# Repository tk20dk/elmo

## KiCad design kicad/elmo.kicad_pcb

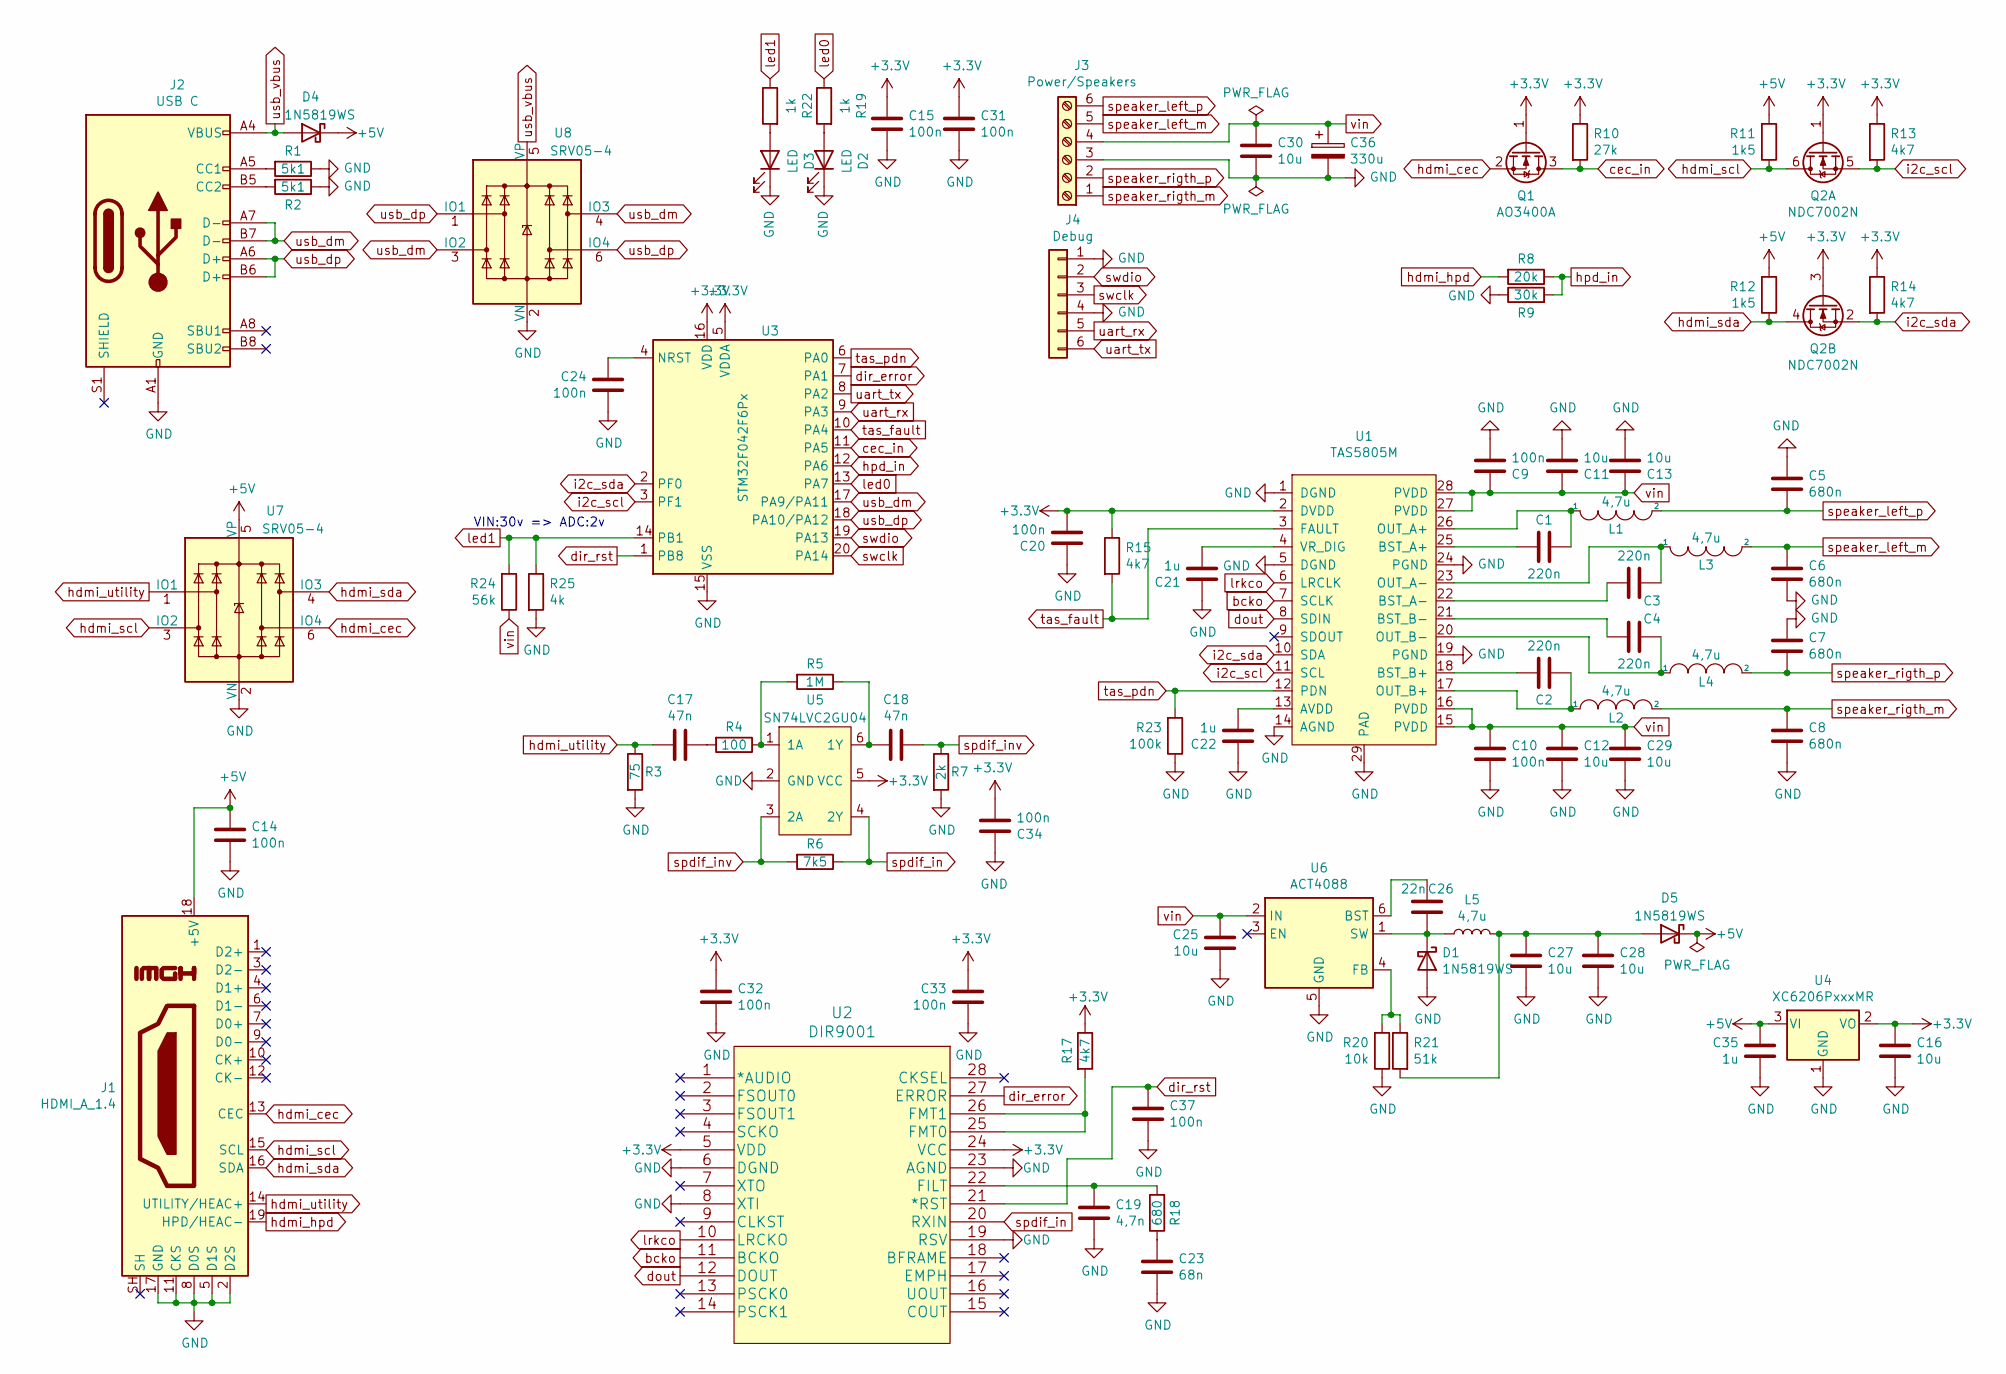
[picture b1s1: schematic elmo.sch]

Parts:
C1, C2, C3, C4: 220n; C_0603_1608Metric
C5, C6, C7, C8: 680n; C_0805_2012Metric
C9, C10, C14, C20: 100n; C_0603_1608Metric
C11, C12, C13, C16, C25, C27, C28, C29, C30: 10u; C_0805_2012Metric
C15, C24, C31, C32, C33, C34, C37: 100n; C_0402_1005Metric
C17, C18: 47n; C_0402_1005Metric
C19: 4,7n; C_0402_1005Metric
C21, C22, C35: 1u; C_0603_1608Metric
C23: 68n; C_0402_1005Metric
C26: 22n; C_0603_1608Metric
C36: 330u; CP_Elec_8x11.9
D1, D4, D5: 1N5819WS; D_SOD-323
D2, D3: LED; LED_0402_1005Metric
J1: HDMI_A_1.4; HDMI_A_19P
J2: USB C; USB_C_Receptacle_XKB_U262-16XN-4BVC11
J3: Power/Speakers; CONN_5MM_01x06
J4: Debug; PinHeader_1x06_P1.27mm_Vertical
L1, L2, L3, L4: 4,7u; L_6.3x6.3_H3
L5: 4,7u; L_4.1x4.1_H1.75
Q1: AO3400A; SOT-23
Q2: NDC7002N; SuperSOT-6
R1, R2: 5k1; R_0402_1005Metric
R3: 75; R_0402_1005Metric
R4: 100; R_0402_1005Metric
R5: 1M; R_0402_1005Metric
R6: 7k5; R_0402_1005Metric
R7: 2k; R_0402_1005Metric
R8: 20k; R_0402_1005Metric
R9: 30k; R_0402_1005Metric
R10: 27k; R_0402_1005Metric
R11, R12: 1k5; R_0402_1005Metric
R13, R14, R15, R17: 4k7; R_0402_1005Metric
R18: 680; R_0402_1005Metric
R19, R22: 1k; R_0402_1005Metric
R20: 10k; R_0402_1005Metric
R21: 51k; R_0402_1005Metric
R23: 100k; R_0402_1005Metric
R24: 56k; R_0402_1005Metric
R25: 4k; R_0402_1005Metric
U1: TAS5805M; HTSSOP-28-1EP_4.4x9.7mm_P0.65mm_EP3.4x9.5mm_Mask2.4x6.17mm_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
U2: DIR9001; TSSOP-28_4.4x9.7mm_P0.65mm
U3: STM32F042F6Px; TSSOP-20_4.4x6.5mm_P0.65mm
U4: XC6206PxxxMR; SOT-23
U5: SN74LVC2GU04; SOT-23-6
U6: ACT4088; SOT-23-6
U7, U8: SRV05-4; SOT-23-6

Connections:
+3V3: C15.1, C16.1, C20.2, C31.1, C32.1, C33.1, C34.2, Q1.1 (G), Q2.1 (G), Q2.3 (G), R10.1, R13.1, R14.1, R15.1, R17.1, U1.2 (DVDD), U2.5 (VDD), U2.24 (VCC), U3.5 (VDDA), U3.16 (VDD), U4.2 (VO), U5.5 (VCC)
+5V: C14.1, C35.1, D4.1 (K), D5.1 (K), J1.18 (+5V), R11.2, R12.2, U4.3 (VI), U7.5 (VP)
GND: C5.1, C6.2, C7.1, C8.2, C9.2, C10.2, C11.2, C12.2, C13.2, C14.2, C15.2, C16.2, C19.2, C20.1, C21.1, C22.1, C23.2, C24.2, C25.2, C27.2, C28.2, C29.2, C30.2, C31.2, C32.2, C33.2, C34.1, C35.2, C36.2, C37.2, D1.2 (A), D2.1 (K), D3.1 (K), J1.2 (D2S), J1.5 (D1S), J1.8 (D0S), J1.11 (CKS), J1.17 (GND), J2.A1 (GND), J2.A12 (GND), J2.B1 (GND), J2.B12 (GND), J3.3, J4.1, J4.4, R1.1, R2.1, R3.2, R7.2, R9.1, R20.1, R23.1, R25.2, U1.1 (DGND), U1.5 (DGND), U1.14 (AGND), U1.19 (PGND), U1.24 (PGND), U1.29 (PAD), U2.6 (DGND), U2.8 (XTI), U2.19 (RSV), U2.23 (AGND), U3.15 (VSS), U4.1 (GND), U5.2 (GND), U6.5 (GND), U7.2 (VN), U8.2 (VN)
unnamed: C1.1, U1.25 (BST_A+)
unnamed: C1.2, L1.1, U1.26 (OUT_A+)
unnamed: C2.1, U1.18 (BST_B+)
unnamed: C2.2, L2.1, U1.17 (OUT_B+)
unnamed: C3.1, U1.22 (BST_A-)
unnamed: C3.2, L3.1, U1.23 (OUT_A-)
unnamed: C4.1, U1.21 (BST_B-)
unnamed: C4.2, L4.1, U1.20 (OUT_B-)
unnamed: C17.1, R4.2
unnamed: C18.1, R5.1, U5.6 (1Y)
unnamed: C19.1, R18.2, U2.22 (FILT)
unnamed: C21.2, U1.4 (VR_DIG)
unnamed: C22.2, U1.13 (AVDD)
unnamed: C23.1, R18.1
unnamed: C24.1, U3.4 (NRST)
unnamed: C26.1, U6.6 (BST)
unnamed: C26.2, D1.1 (K), L5.1, U6.1 (SW)
unnamed: C27.1, C28.1, D5.2 (A), L5.2, R21.2
unnamed: D2.2 (A), R19.2
unnamed: D3.2 (A), R22.2
unnamed: J2.A5 (CC1), R1.2
unnamed: J2.B5 (CC2), R2.2
unnamed: R4.1, R5.2, U5.1 (1A)
unnamed: R17.2, U2.25 (FMT0), U2.26 (FMT1)
unnamed: R20.2, R21.1, U6.4 (FB)
bcko: U1.7 (SCLK), U2.11 (BCKO)
cec_in: Q1.3 (D), R10.2, U3.11 (PA5)
dir_error: U2.27 (ERROR), U3.7 (PA1)
dir_rst: C37.1, U2.21 (*RST), U3.1 (PB8)
dout: U1.8 (SDIN), U2.12 (DOUT)
hdmi_cec: J1.13 (CEC), Q1.2 (S), U7.6 (IO4)
hdmi_hpd: J1.19 (HPD/HEAC-), R8.2
hdmi_scl: J1.15 (SCL), Q2.6 (D), R11.1, U7.3 (IO2)
hdmi_sda: J1.16 (SDA), Q2.4 (D), R12.1, U7.4 (IO3)
hdmi_utility: C17.2, J1.14 (UTILITY/HEAC+), R3.1, U7.1 (IO1)
hpd_in: R8.1, R9.2, U3.12 (PA6)
i2c_scl: Q2.5 (S), R13.2, U1.11 (SCL), U3.3 (PF1)
i2c_sda: Q2.2 (S), R14.2, U1.10 (SDA), U3.2 (PF0)
led0: R19.1, U3.13 (PA7)
led1: R22.1, R24.2, R25.1, U3.14 (PB1)
lrkco: U1.6 (LRCLK), U2.10 (LRCKO)
spdif_in: R6.1, U2.20 (RXIN), U5.4 (2Y)
spdif_inv: C18.2, R6.2, R7.1, U5.3 (2A)
speaker_left_m: C6.1, J3.5, L3.2
speaker_left_p: C5.2, J3.6, L1.2
speaker_rigth_m: C8.1, J3.1, L2.2
speaker_rigth_p: C7.2, J3.2, L4.2
swclk: J4.3, U3.20 (PA14)
swdio: J4.2, U3.19 (PA13)
tas_fault: R15.2, U1.3 (FAULT), U3.10 (PA4)
tas_pdn: R23.2, U1.12 (PDN), U3.6 (PA0)
uart_rx: J4.5, U3.9 (PA3)
uart_tx: J4.6, U3.8 (PA2)
usb_dm: J2.A7 (D-), J2.B7 (D-), U3.17 (PA9/PA11), U8.3 (IO2), U8.4 (IO3)
usb_dp: J2.A6 (D+), J2.B6 (D+), U3.18 (PA10/PA12), U8.1 (IO1), U8.6 (IO4)
usb_vbus: D4.2 (A), J2.A4 (VBUS), J2.A9 (VBUS), J2.B4 (VBUS), J2.B9 (VBUS), U8.5 (VP)
vin: C9.1, C10.1, C11.1, C12.1, C13.1, C25.1, C29.1, C30.1, C36.1, J3.4, R24.1, U1.15 (PVDD), U1.16 (PVDD), U1.27 (PVDD), U1.28 (PVDD), U6.2 (IN)

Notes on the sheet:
VIN:30v => ADC:2v

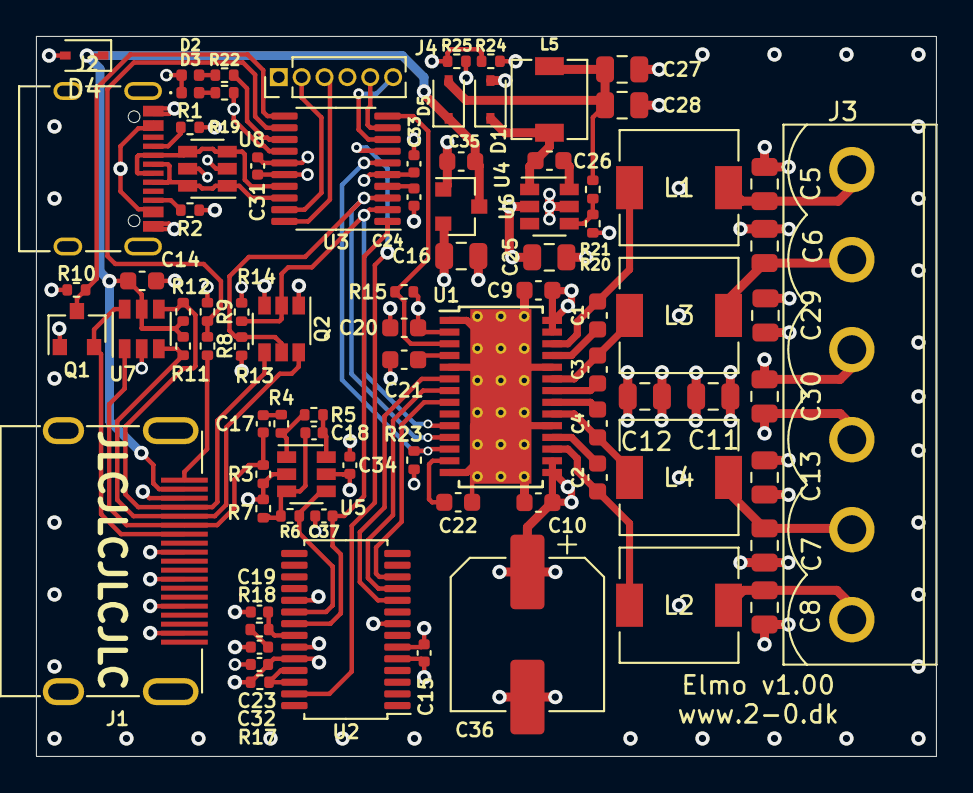
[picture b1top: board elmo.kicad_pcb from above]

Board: 4 copper layers, 50.0 x 40.0 mm, 85 parts (0 on the bottom side), 60 nets.

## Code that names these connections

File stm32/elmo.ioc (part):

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Mcu.Name=STM32F042F6Px
Mcu.Package=TSSOP20
Mcu.UserName=STM32F042F6Px
PA0.GPIOParameters=GPIO_Label
PA0.GPIO_Label=TAS_PDN
PA0.Signal=GPIO_Output
PA1.GPIOParameters=GPIO_PuPd,GPIO_Label
PA1.GPIO_Label=DIR_ERROR
PA1.GPIO_PuPd=GPIO_PULLUP
PA1.Signal=GPIO_Input
PA11.Mode=Device
PA11.Signal=USB_DM
PA12.Mode=Device
PA12.Signal=USB_DP
PA13.Mode=Serial_Wire
PA13.Signal=SYS_SWDIO
PA14.Mode=Serial_Wire
PA14.Signal=SYS_SWCLK
PA2.Mode=Asynchronous
PA2.Signal=USART2_TX
PA3.GPIOParameters=GPIO_PuPd
PA3.GPIO_PuPd=GPIO_PULLUP
PA3.Mode=Asynchronous
PA3.Signal=USART2_RX
PA4.GPIOParameters=GPIO_PuPd,GPIO_Label
PA4.GPIO_Label=TAS_FAULT
PA4.GPIO_PuPd=GPIO_PULLUP
PA4.Signal=GPIO_Input
PA5.GPIOParameters=GPIO_Label
PA5.GPIO_Label=CEC_IN
PA5.Mode=CEC_Activate
PA5.Signal=CEC
PA6.GPIOParameters=GPIO_Label
PA6.GPIO_Label=HPD_IN
PA6.Signal=GPIO_Input
PA7.GPIOParameters=GPIO_Label
PA7.GPIO_Label=HMI_LED0
PA7.Signal=GPIO_Output
PB1.GPIOParameters=GPIO_Label
PB1.GPIO_Label=HMI_LED1
PB1.Mode=IN9
PB1.Signal=ADC_IN9
PB8.GPIOParameters=GPIO_Label
PB8.GPIO_Label=DIR_RST
PB8.Signal=GPIO_Output
PF0-OSC_IN.Mode=I2C
PF0-OSC_IN.Signal=I2C1_SDA
PF1-OSC_OUT.Mode=I2C
PF1-OSC_OUT.Signal=I2C1_SCL
RCC.SYSCLKFreq_VALUE=48000000
RCC.SYSCLKSource=RCC_SYSCLKSOURCE_HSI48
board=custom

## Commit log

2021-04-25 Elmo v1.00
